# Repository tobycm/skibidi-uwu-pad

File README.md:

# skibidi-uwu-pad

me when i osu

## features:

- 3 hall effects switches
- 2 cherry mx switches
- 1 rotary encoder with push function
- rgb underglow
- hot swappable keycaps
- customizable firmware via zmk
- usb/bluetooth connectivity
- 3.7V li-ion battery
- smart battery power saving mode

## renders:

## schematic

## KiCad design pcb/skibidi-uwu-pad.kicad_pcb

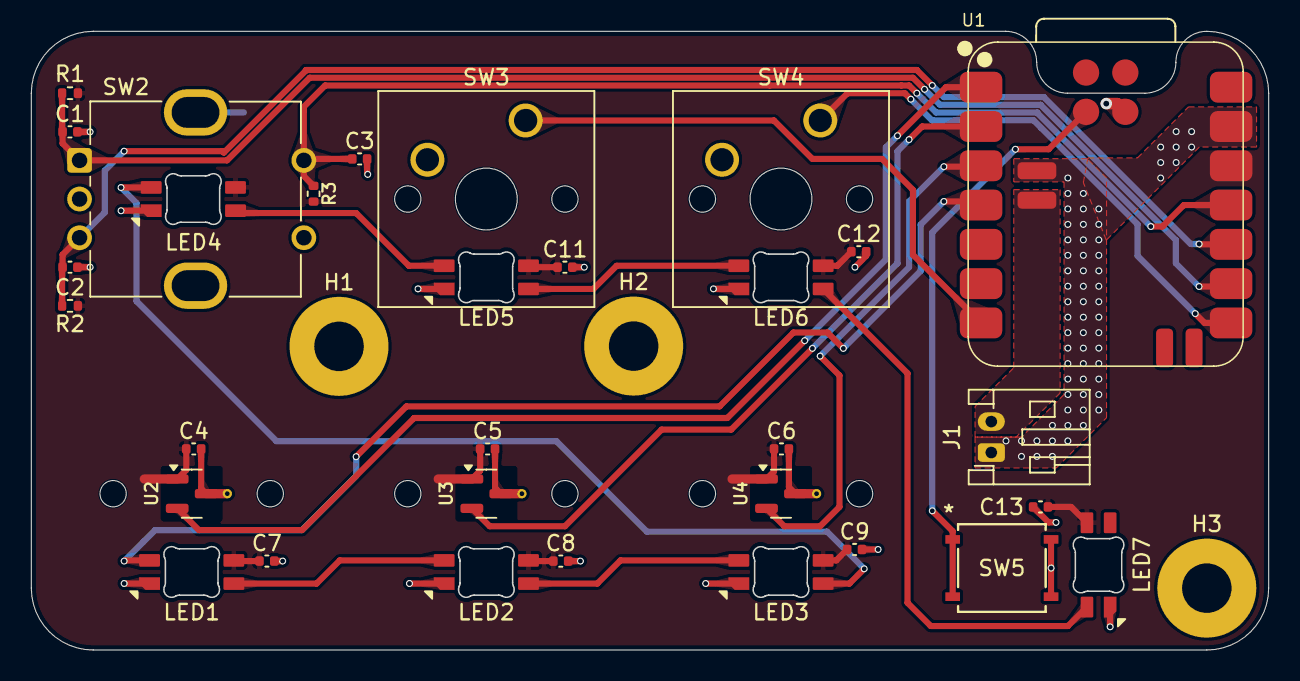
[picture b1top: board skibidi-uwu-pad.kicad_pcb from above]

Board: 2 copper layers, 80.0 x 40.0 mm, 34 parts (0 on the bottom side), 19 nets.

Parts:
C1, C2, C3, C4, C5, C6, C7, C8, C9, C11, C12, C13: 100n; C_0402_1005Metric
H1, H2, H3: MountingHole; MountingHole_3.2mm_M3_Pad
J1: Conn_01x02_Socket; JST_PH_S2B-PH-K_1x02_P2.00mm_Horizontal
LED1, LED2, LED3, LED5, LED6: MX_SK6812MINI-E; LED_MX_6028R
LED4, LED7: SK6812MINI-E; LED_6028R
R1, R2, R3: 10k; R_0402_1005Metric
SW2: RotaryEncoder_Switch; RotaryEncoder_Bourns_Vertical_PEC12R-3x17F-Sxxxx
SW3, SW4: SW_Push; SW_Cherry_MX_1.00u_PCB
SW5: PTS526 SM15 SMTR2 LFS; SON4_PTS526 SM15 SMTR2 LFS_CNK
U1: XIAO-nRF52840-SMD
U2, U3, U4: AH49FNTR-G1; SW_MX_HE_0deg_1u

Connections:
+3.3V: C4.1, C5.1, C6.1, C7.1, C8.1, C9.1, C11.1, C12.1, C13.1, LED1.1 (VDD), LED2.1 (VDD), LED3.1 (VDD), LED4.1 (VDD), LED5.1 (VDD), LED6.1 (VDD), LED7.1 (VDD), R1.1, R2.1, R3.1, U1.12 (3V3), U2.1 (VCC), U3.1 (VCC), U4.1 (VCC)
/A0: U1.1 (P0.02_A0_D0), U2.2 (OUT)
/A1: U1.2 (P0.03_A1_D1), U3.2 (OUT)
/A2: U1.3 (P0.28_A2_D2), U4.2 (OUT)
/A3: LED1.3 (DIN), U1.4 (P0.29_A3_D3)
/D6: SW3.1, U1.7 (P1.11_D6_TX)
/D7: SW4.1, U1.8 (P1.12_D7_RX)
/D8: C1.1, R1.2, SW2.A, U1.9 (P1.13_D8_SCK)
/D9: C2.1, R2.2, SW2.B, U1.10 (P1.14_D9_MISO)
/D10: C3.1, R3.2, SW2.S1, U1.11 (P1.15_D10_MOSI)
/RESET: SW5.1, SW5.2, U1.21 (RESET)
GND: C1.2, C2.2, C3.2, C4.2, C5.2, C6.2, C7.2, C8.2, C9.2, C11.2, C12.2, C13.2, J1.1, LED1.4 (VSS), LED2.4 (VSS), LED3.4 (VSS), LED4.4 (VSS), LED5.4 (VSS), LED6.4 (VSS), LED7.4 (VSS), SW2.C, SW2.S2, SW3.2, SW4.2, SW5.3, SW5.4, U1.13 (GND), U1.16 (GND), U1.22 (GND), U2.3 (GND), U3.3 (GND), U4.3 (GND)
unnamed: J1.2, U1.15 (BAT)
unnamed: LED1.2 (DOUT), LED2.3 (DIN)
unnamed: LED2.2 (DOUT), LED3.3 (DIN)
unnamed: LED3.2 (DOUT), LED4.3 (DIN)
unnamed: LED4.2 (DOUT), LED5.3 (DIN)
unnamed: LED5.2 (DOUT), LED6.3 (DIN)
unnamed: LED6.2 (DOUT), LED7.3 (DIN)

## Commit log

2025-11-08 PoC done!
2025-11-08 forgor to add pcb :skull:
2025-11-08 dummy ahh left the lock file
2025-11-08 update readme + add firmware
2025-11-09 add smart power saving circuit + update readme
2025-11-09 make a fancy case whoaaaaa
2025-11-09 update bom
2025-11-11 add cool open source hardware logo
2025-12-15 add schematic
